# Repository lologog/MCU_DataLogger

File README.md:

# MCU Data Logger

## Project description
In many embedded systems, there is often a lack of non-volatile or a dedicated mechanism for long-term data logging. Sensor readings, digital signals or communication data are frequently lost or must be transmitted in real time, which can be inconvenient or require constant infrastructure.

To address this limitation, I developed a compact data logger that acts as an independent module capable of storing data for later analysis. The device can capture data from digital or receive custom data frames sent by other devices via a communication bus.

## Project Goals and Scope 
- Design and build a complete embedded data-logging system including hardware, firmware and mechanical design.
- Capture data from digital inputs or communication frames transmitted over a bus.
- Store data safely in non-volatile memory (using internal CPU EEPROM or two external I<sup>2</sup>C chips).
- Provide a user interface for operation control and system status.
- Include a custom 3D-printed enclosure to protect the electronics and ensure ease of installation.

## Hardware design
The hardware is build around an ATmega328p microcontroller running with an external 16MHz crystal oscillator, ensuring stable and precise timing for all operations.
Data may be stored in two external 24LC1025 I<sup>2</sup>C EEPROM chips, which provide a large amount of non-volatile memory for long-term data logging. An additional DS1337S+ RTC module keeps accurate time for timestamping logged events.

The board includes two LEDs: one serves as a power indicator, while the second is user-programmable and can be freely controlled by the firmware for signaling various system states.
External connection are provided for 5 V power input, six digital inputs and accompanying +5 V and GND rails for convenient sensor or signal wiring. Communication and programming interfaces are also available through UART, I<sup>2</sup>C and SPI/ICSP headers.

The PCB has been designed with mechanical integration in mind.
It can be easily mounted inside the custom 3D-printed enclosure, with precisely aligned M2 mounting holes and standoff positions that provide a secure fit between the base and the upper part of the case.

*3D render of the PCB board made in KiCad software*

---

*Finished PCB board*

---

*PCB board with bottom part of the enclosure*

---

*Assembled device*

---

## Example Application - Office Window Monitor
To demonstrate the flexibility of the MCU Data Logger platform, a sample firmware project project was implemented for monitoring office windows.

The system uses six magnetic reed switches (contact sensors) connected to the digital inputs of the board. It continuously monitors each window's state, counts the number of openings and calculates the total time each window remains open.

### Communication Interface (UART)
The device communicates with a PC via UART, accepting three command codes:
- '1' - Sends the current window states , total number of openings and total open time for each channel.
- '2' - Resets all data stored in EEPROM and RAM.
- '3' - Prints the system uptime since power-on.

This allows the user to easily monitor and control the logger from a serial console or custom PC software.

### Firmware structure
The firmware was written entirely in C and designed to be modular, reusable and easy to extend for different data-logging applications. 
It is divided into two layers: a set of core low-level drivers and an application layer implementing the example project logic.

#### Core drivers
These modules provide essential hardware functionality and can be reused across multiple projects built on this platform:
- **i2c.c / i2c.h** - Communication with external 24LC1025 EEPROMs and the DS1337S+ RTC module via I<sup>2</sup>C bus
- **uart.c / uart.h** - UART serial interface for communication with a PC or other microcontrollers
- **eeprom.c / eeprom.h** - Management of non-volatile internal data storage
- **rtc.c / rtc.h** - Real-time clock driver providing precise timekeeping and timestamps

#### Application layer
This section implements the Office Window Monitor example, showcasing how the data logger can be adapted to real-world tasks:
- **windows.c / windows.h** - Detects window openings, counts events and measures how long each window remains open.
- **console.c / console.h** - handles UART command parsing and formatted data output for the serial console.

### Example UART Output
<div align="center">
  
</div>

After startup, the device displays basic information such as firmware version, UART settings and available commands.
The first readout shows the initial state where all windows are closed.
After a short time, another read reveals that window 2 and 6 have been opened several times, with their total open duration displayed.
Next, the system uptime is requested and shown as 00:00:43.
Finally, the reset command is issued, clearing all stored data - the last read confirms that all counters and timers have returned to zero.

## Reusability and Development Notes
- The device operates from a 5 V power supply, which can be provided through the main power connector on the left side of the board or directly from the ICSP header during programming or testing.
- Firmware is programmed via the ICSP interface, and in this project the board was flashed using a USBasp HW-437 programmer.
- For serial communication and debugging, a USB-UART converter (FT232) was used to connect the logger to a PC terminal.

## Author
- Name: Krzysztof Tomicki
- Contact: [tomicki.krzysztof.pv@gmail.com](mailto:tomicki.krzysztof.pv@gmail.com)

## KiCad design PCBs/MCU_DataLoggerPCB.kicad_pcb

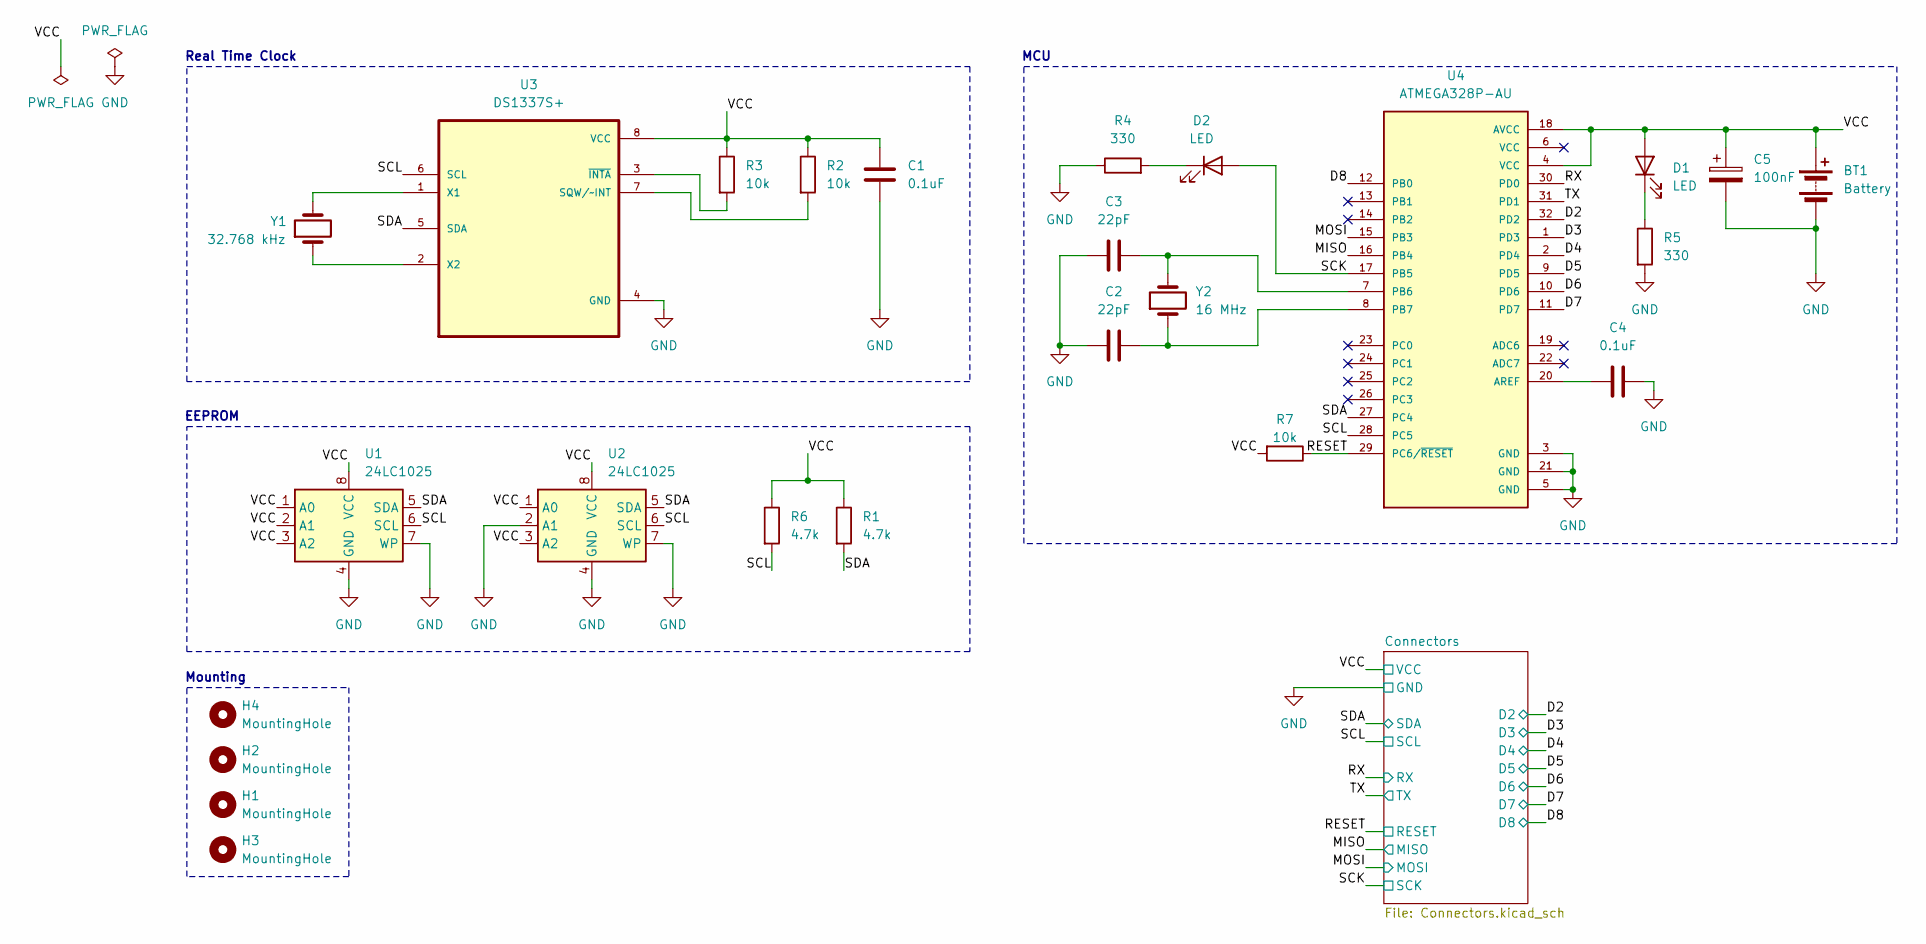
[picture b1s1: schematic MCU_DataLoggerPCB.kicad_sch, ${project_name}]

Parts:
BT1: Battery; PinHeader_1x02_P2.54mm_Vertical
C1, C4: 0.1uF; C_0805_2012Metric_Pad1.18x1.45mm_HandSolder
C2, C3: 22pF; C_0805_2012Metric_Pad1.18x1.45mm_HandSolder
C5: 100nF; C_0805_2012Metric_Pad1.18x1.45mm_HandSolder
D1, D2: LED; LED_0805_2012Metric_Pad1.15x1.40mm_HandSolder
H1, H2, H3, H4: MountingHole; MountingHole_2.2mm_M2
R1, R6: 4.7k; R_0805_2012Metric_Pad1.20x1.40mm_HandSolder
R2, R3, R7: 10k; R_0805_2012Metric_Pad1.20x1.40mm_HandSolder
R4, R5: 330; R_0805_2012Metric_Pad1.20x1.40mm_HandSolder
U1, U2: 24LC1025; SOIC-8_5.3x5.3mm_P1.27mm
U3: DS1337S+; SOIC127P600X175-8N
U4: ATMEGA328P-AU; QFP80P900X900X120-32N; PARTREV 8271A
Y1: 32.768 kHz; Crystal_SMD_3215-2Pin_3.2x1.5mm
Y2: 16 MHz; Crystal_SMD_5032-2Pin_5.0x3.2mm_HandSoldering

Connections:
/D2: U4.32 (PD2); also elsewhere on the board
/D3: U4.1 (PD3); also elsewhere on the board
/D4: U4.2 (PD4); also elsewhere on the board
/D5: U4.9 (PD5); also elsewhere on the board
/D6: U4.10 (PD6); also elsewhere on the board
/D7: U4.11 (PD7); also elsewhere on the board
/D8: U4.12 (PB0); also elsewhere on the board
/MISO: U4.16 (PB4); also elsewhere on the board
/MOSI: U4.15 (PB3); also elsewhere on the board
/RESET: R7.1, U4.29 (PC6/~RESET); also elsewhere on the board
/RX: U4.30 (PD0); also elsewhere on the board
/SCK: D2.2 (A), U4.17 (PB5); also elsewhere on the board
/SCL: R6.2, U1.6 (SCL), U2.6 (SCL), U3.6 (SCL), U4.28 (PC5); also elsewhere on the board
/SDA: R1.2, U1.5 (SDA), U2.5 (SDA), U3.5 (SDA), U4.27 (PC4); also elsewhere on the board
/TX: U4.31 (PD1); also elsewhere on the board
/VCC: BT1.1 (+), C1.1, C5.1, D1.2 (A), R1.1, R2.1, R3.1, R6.1, R7.2, U1.1 (A0), U1.2 (A1), U1.3 (A2), U1.8 (VCC), U2.1 (A0), U2.3 (A2), U2.8 (VCC), U3.8 (VCC), U4.4 (VCC), U4.18 (AVCC); also elsewhere on the board
GND: BT1.2 (-), C1.2, C2.1, C3.1, C4.2, C5.2, R4.1, R5.2, U1.4 (GND), U1.7 (WP), U2.2 (A1), U2.4 (GND), U2.7 (WP), U3.4 (GND), U4.3 (GND), U4.5 (GND), U4.21 (GND); also elsewhere on the board
unnamed: D1.1 (K), R5.1
unnamed: D2.1 (K), R4.2
unnamed: R2.2, U3.7 (SQW/~INT)
unnamed: U3.1 (X1), Y1.2
unnamed: U3.2 (X2), Y1.1
unnamed: R3.2, U3.3 (~INTA)
unnamed: C4.1, U4.20 (AREF)
unnamed: C3.2, U4.7 (PB6), Y2.2
unnamed: C2.2, U4.8 (PB7), Y2.1

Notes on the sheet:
Real Time Clock
EEPROM
MCU
Mounting

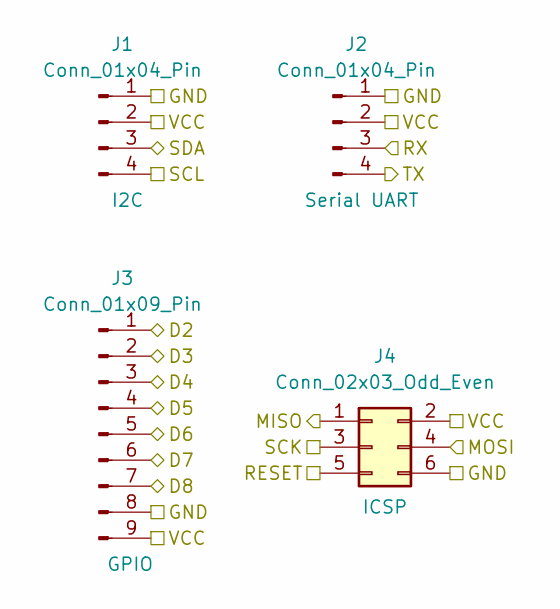
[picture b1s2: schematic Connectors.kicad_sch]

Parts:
J1, J2: Conn_01x04_Pin; PinHeader_1x04_P2.54mm_Vertical
J3: Conn_01x09_Pin; PinHeader_1x09_P2.54mm_Vertical
J4: Conn_02x03_Odd_Even; PinHeader_2x03_P2.54mm_Vertical

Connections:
/D2: J3.1; also elsewhere on the board
/D3: J3.2; also elsewhere on the board
/D4: J3.3; also elsewhere on the board
/D5: J3.4; also elsewhere on the board
/D6: J3.5; also elsewhere on the board
/D7: J3.6; also elsewhere on the board
/D8: J3.7; also elsewhere on the board
/MISO: J4.1; also elsewhere on the board
/MOSI: J4.4; also elsewhere on the board
/RESET: J4.5; also elsewhere on the board
/RX: J2.3; also elsewhere on the board
/SCK: J4.3; also elsewhere on the board
/SCL: J1.4; also elsewhere on the board
/SDA: J1.3; also elsewhere on the board
/TX: J2.4; also elsewhere on the board
/VCC: J1.2, J2.2, J3.9, J4.2; also elsewhere on the board
GND: J1.1, J2.1, J3.8, J4.6; also elsewhere on the board

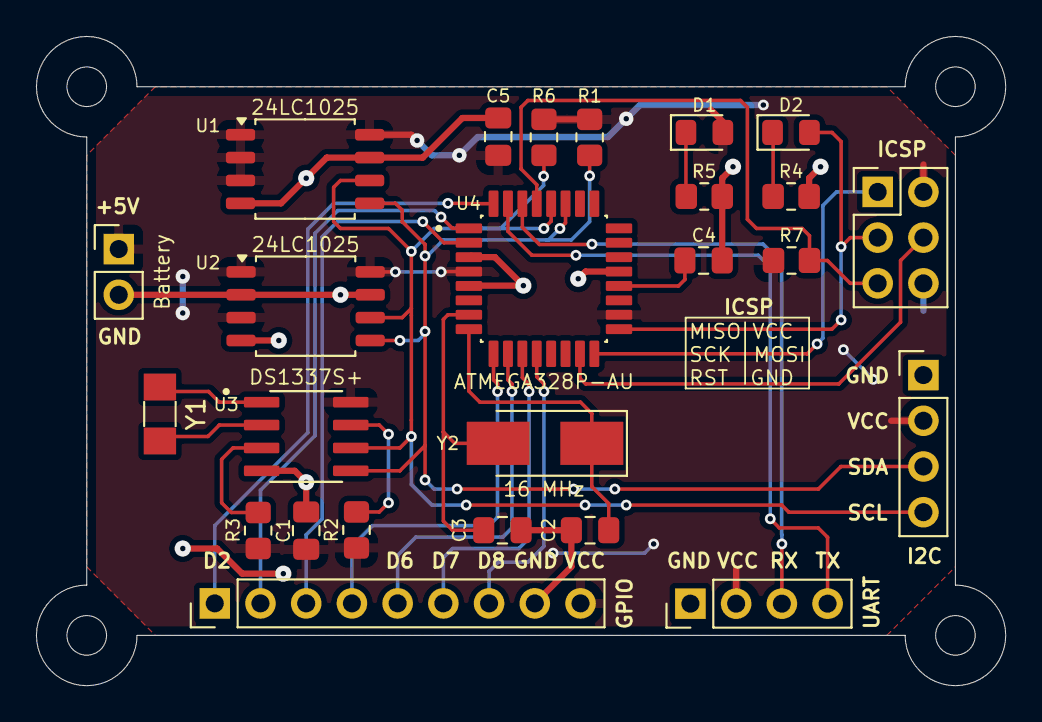
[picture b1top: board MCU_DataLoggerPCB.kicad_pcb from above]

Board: 2 copper layers, 53.8 x 36.1 mm, 29 parts (0 on the bottom side), 26 nets.

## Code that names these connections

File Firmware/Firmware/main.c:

/*
 * Firmware.c
 *
 * Created: 19.10.2025 14:58:19
 * Author : Krzysztof Tomicki
 * Description: Main file
 */

#define F_CPU 16000000UL

#include <avr/io.h>
#include <util/delay.h>
#include <stdio.h>
#include <string.h>
#include <avr/eeprom.h>

#include "uart.h"
#include "i2c.h"
#include "rtc.h"
#include "console.h"
#include "windows.h"
#include "config.h"
#include "eeprom.h"

const uint8_t window_pins[WINDOW_COUNT] =
{
	PD2, PD3, PD4, PD5, PD6, PD7
};

window_data_t windows[WINDOW_COUNT];
uint32_t boot_unix = 0;

int main(void) 
{
	UART_init(103); //9600 baud at 16 MHz
	I2C_init();
	init_windows();
	print_banner();
	
	boot_unix = rtc_get_unix();
	
	while (1)
	{
		uint32_t now = rtc_get_unix();
		
		update_windows(now);
		uart_console(now);
	
		_delay_ms(LOOP_MS);
	}
}

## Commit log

2025-03-08 Project: Kicad project initialization
2025-03-10 Project: clean configured project to start the work
2025-03-10 Project: add symbols to the schematic sheets
2025-03-10 Project: change location of symbols
2025-03-10 Project: add component values
2025-03-10 Project: completed symbol-footprint associations
2025-03-10 Project: completed wiring of the main sheet
2025-03-10 Project: completed wiring the second sheet
2025-03-10 Project: Allocated GND and VCC to the Power net class
2025-03-10 Project: change location of the power flags
2025-03-10 Project: completed comments
2025-03-10 Project: Setup PCB
2025-03-10 Project: Completed placement of the footprints
2025-03-10 Project: add routes to the PCB
2025-03-10 Project: small modifications in routing
2025-03-11 Project: Completed putting silkscreen on the PCB
2025-03-11 Project: Fix defect with SCK and SCL clocks in the schematic
2025-03-11 Project: Fixed the same error but on PCB
2025-03-11 Project: PCB ready for manufacturing
2025-03-11 Project: add 3D shapes
2025-03-11 Project: Completed 2 layer PCB
2025-03-11 Project: Added gerber directiories to gitignore
2025-03-11 Project: Completed 4-layer PCB routing
2025-03-11 Project: Correcting thickness of VCC routes
2025-03-11 Project: Added gitattributes file to ignore PCB files during merge
2025-03-11 Project: correctint file order in the repository
2025-03-11 Project: Fixing file order in the repository
2025-03-11 Project: Fixing files order in the perository
2025-03-11 Project: Add 3D render photo
2025-03-11 README: add 3D render photo
2025-03-12 Project: Added BOM and changed 32.768kHz crystal footprint to match element that was available to buy at the moment
2025-03-27 Project: add soldiered PCB photo
2025-03-27 README: add soldiered PCB photo
2025-03-28 README: add work in progress information
2025-03-29 PROJECT: example blink code to test if the ATMega can be programed correctly
2025-03-29 PROJECT: add UART communication
2025-03-29 PROJECT: added I2C libraries and succesfully read time from RTC module
2025-03-29 PROJECT: extracting RTC functions from main.c to dedicated library
2025-03-29 PROJECT: add library to write data to EEPROM (DS1337S+) and change main to read all GPIOs state and then save it to EEPROM and print it via UART
2025-10-14 Project: Add photo of board with the cover
2025-10-14 Project: Add photo to README
2025-10-15 Project: add photo of board with bottom and top
2025-10-15 Rename IMG_3039.jpg to finished-cover
2025-10-15 README: add full cover to README
2025-10-15 Project: add enclosure folder
2025-10-19 Main: set pull ups on DI and switch processing logic to have software pull-downs
2025-10-19 RTC: add i2c.h include
2025-10-19 All devices tested - from now on all logging codes will be on different branches
2025-10-19 CLEAN PROJECT
2025-10-19 Main: add RTC and DI reading
2025-10-19 Main: set default measurement data as 0
2025-10-19 RTC: add rtc_get_unix function
2025-10-19 Main: calculate all window related data
2025-10-19 Main: set defines for loop time to avoid using raw numbers in code
2025-10-19 EEPROM: delete old EEPROM library
2025-10-19 Main: store windows data in EEPROM
2025-10-19 Main: add UART control from PC
2025-10-19 Project: change main functions locations across files to clear main.c
2025-10-20 Project: delete q file
2025-10-26 [Images] add Terminal screenshot of the program
2025-10-26 [Images] rename photo of the board alone
2025-10-26 [Images] delete old board alone photo
2025-10-26 [Images] rename finished-cover photo to add .jpg at the end of the name
2025-10-26 [README] add device specification description
2025-10-26 [README] add window project explanation
    Corrected typos and improved clarity in the README.
2025-10-27 [README] fix UART output screenshot alignment in README
    Updated image display formatting in README.
2025-11-02 Add MIT License to the project
